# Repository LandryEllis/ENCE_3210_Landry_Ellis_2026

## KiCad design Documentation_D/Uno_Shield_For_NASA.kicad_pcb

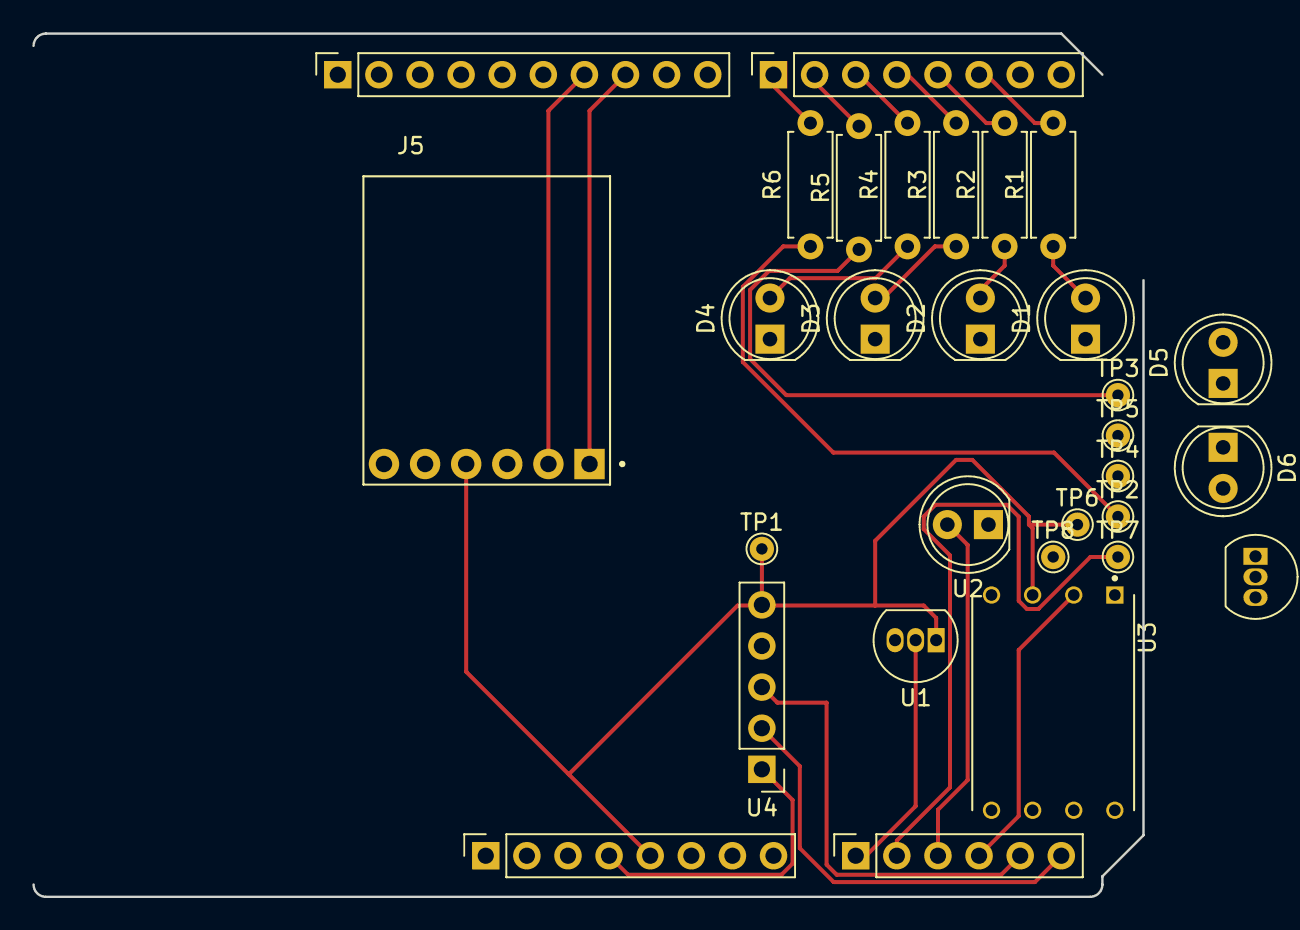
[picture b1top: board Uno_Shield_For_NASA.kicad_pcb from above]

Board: 2 copper layers, 68.6 x 53.3 mm, 30 parts (0 on the bottom side), 24 nets.

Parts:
D1: LED1_Onboard; LED_D5.0mm
D2: LED2_Onboard; LED_D5.0mm
D3: LED3_Onboard; LED_D5.0mm
D4: LED4_Onboard; LED_D5.0mm
D5: LED5_Remote; LED_D5.0mm
D6: LED6_Remote; LED_D5.0mm
J1: Power; PinSocket_1x08_P2.54mm_Vertical
J2: Digital/PWM; PinSocket_1x10_P2.54mm_Vertical
J3: Analog; PinSocket_1x06_P2.54mm_Vertical
J4: Digital/PWM; PinSocket_1x08_P2.54mm_Vertical
J5: OpenLog_MicroSD; MODULE_DEV-13955
R1, R2, R3, R4, R5, R6: 330; R_Axial_DIN0207_L6.3mm_D2.5mm_P7.62mm_Horizontal
TP1, TP2, TP3, TP4, TP6, TP7, TP8: ACC_Z_TestPoint; TestPoint_THTPad_D1.5mm_Drill0.7mm
TP5: GND; TestPoint_THTPad_D1.5mm_Drill0.7mm
U1: TMP36_Internal_A0; TO-92_Inline
U2: Humidity_A2; LED_D5.0mm
U3: Pressure_A3; DIP1330W46P254L1000H544Q8
U4: ADXL335_XY_A4_A5; PinHeader_1x05_P2.54mm_Vertical
U5: TMP36_External_A1; TO-92_Inline

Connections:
+3V3: J1.4, U4.1 (VCC)
+5V: J1.5, J5.4, TP6.1, U1.1 (Vs), U3.3 (OUT), U5.1 (Vs)
/A0: J3.1, U1.2 (Vout)
/A1: J3.2, TP7.1, U5.2 (Vout)
/A2: J3.3, U2.2 (OUT)
/A3: J3.4, U3.2 (Vs)
/A4: J3.5, U4.3 (X)
/A5: J3.6, U4.2 (GND)
/ACC_Z_SPARE: TP1.1, U4.5 (Z)
/D2: J4.6, R1.2
/D3: J4.5, R2.2
/D4: J4.4, R3.2
/D5: J4.3, R4.2
/D6: J4.2, R5.2
/D7: J4.1, R6.2
/D10: J2.8, J5.1
/D11: J2.7, J5.2
GND: D1.1 (K), D2.1 (K), D3.1 (K), D4.1 (K), D5.1 (K), D6.1 (K), J1.6, J1.7, J2.4, J5.3, TP4.1, TP5.1, TP8.1, U1.3 (GND), U2.1 (VCC), U3.1 (NC), U4.4 (Y), U5.3 (GND)
unnamed: D1.2 (A), R1.1
unnamed: D2.2 (A), R2.1
unnamed: D3.2 (A), R3.1
unnamed: D4.2 (A), R4.1
unnamed: D5.2 (A), R5.1, TP3.1
unnamed: D6.2 (A), R6.1, TP2.1

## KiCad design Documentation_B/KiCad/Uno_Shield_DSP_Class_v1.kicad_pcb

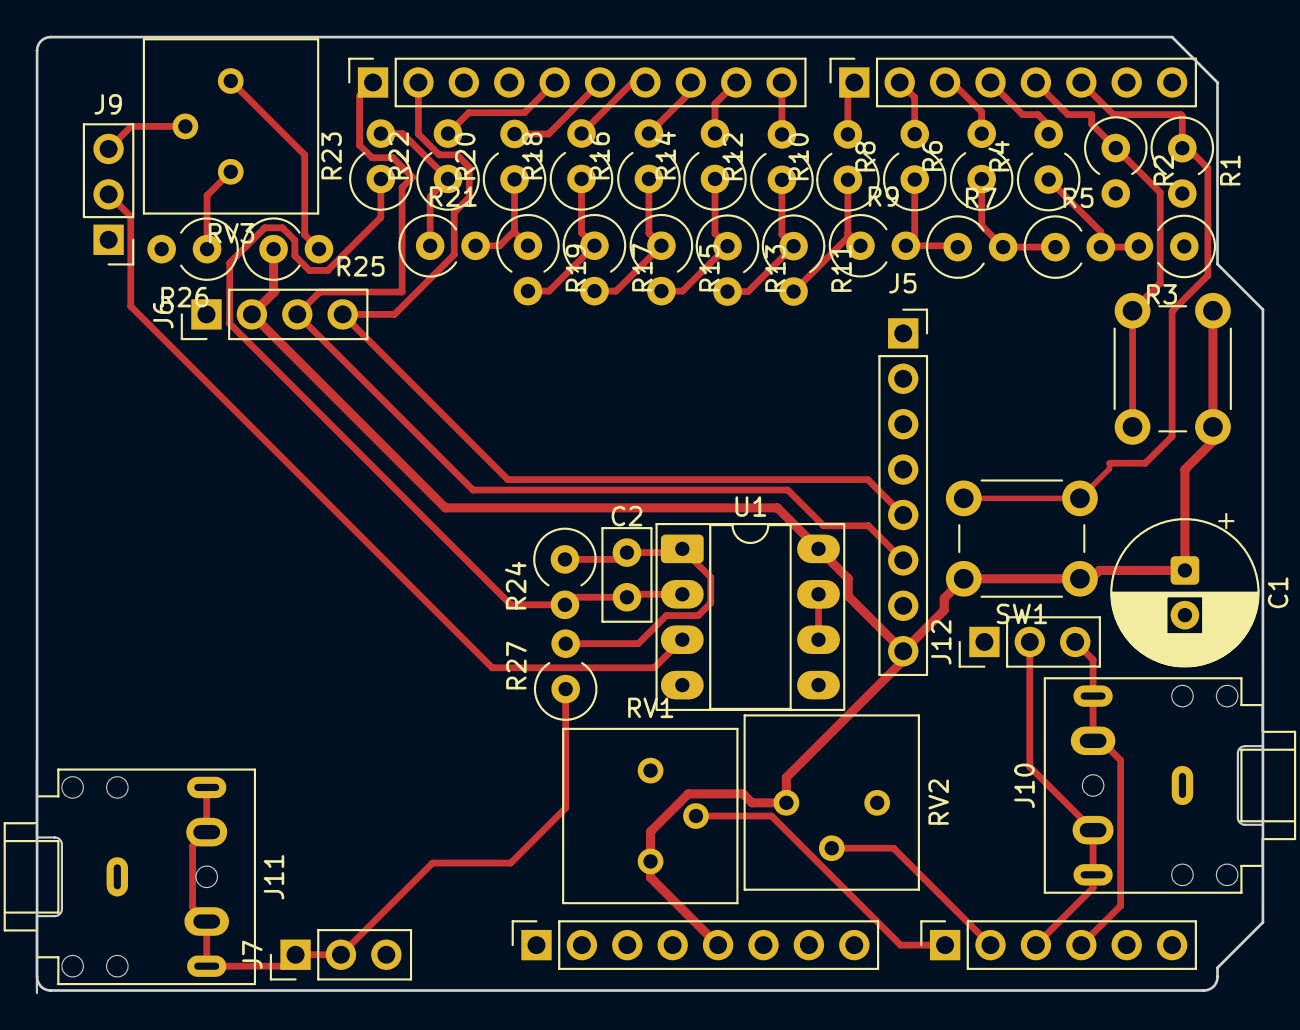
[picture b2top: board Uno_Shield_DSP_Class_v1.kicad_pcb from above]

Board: 2 copper layers, 68.6 x 53.3 mm, 46 parts (0 on the bottom side), 38 nets.

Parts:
C1: 47uF; CP_Radial_D8.0mm_P2.50mm
C2: 100pF; C_Disc_D5.0mm_W2.5mm_P2.50mm
J1: Power; PinSocket_1x08_P2.54mm_Vertical
J2: Digital/PWM; PinSocket_1x10_P2.54mm_Vertical
J3: Analog; PinSocket_1x06_P2.54mm_Vertical
J4: Digital/PWM; PinSocket_1x08_P2.54mm_Vertical
J5: IMU_CONN; PinSocket_1x08_P2.54mm_Vertical
J6: SCREEN_CONN; PinHeader_1x04_P2.54mm_Vertical
J7: AUDIO_OUT; PinHeader_1x03_P2.54mm_Vertical
J9: JUMPER; PinHeader_1x03_P2.54mm_Vertical
J10, J11: AudioJack5; Jack_3.5mm_CUI_SJ1-3525N_Horizontal
J12: AUDIO_IN; PinHeader_1x03_P2.54mm_Vertical
R1, R2: 100k; R_Axial_DIN0309_L9.0mm_D3.2mm_P2.54mm_Vertical
R3, R4, R6, R8, R10, R12, R14, R16, R18, R20, R22, R23, R24, R25, R26: 20k; R_Axial_DIN0309_L9.0mm_D3.2mm_P2.54mm_Vertical
R5, R7, R9, R11, R13, R15, R17, R19, R21: 10k; R_Axial_DIN0309_L9.0mm_D3.2mm_P2.54mm_Vertical
R27: 1k; R_Axial_DIN0309_L9.0mm_D3.2mm_P2.54mm_Vertical
RV1, RV2, RV3: 100k; Potentiometer_Bourns_3386P_Vertical
SW1: BT_1; SW_PUSH_6mm
SW2: BT_2; SW_PUSH_6mm
U1: MCP6002-xP; DIP-8_W7.62mm_Socket_LongPads

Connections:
+5V: C1.1, J1.5, J5.8, J6.2, R25.1, RV1.1, RV2.1, SW1.1, SW2.1, U1.8 (V+)
/A0: J3.1, RV1.2
/A1: J3.2, RV2.2
/AUDIO_OUT: J7.1, J7.2, J11.R, J11.RN, J11.T, J11.TN, R27.1
/BT1: J4.6, R1.1, SW1.2
/BT2: J4.5, R2.1, SW2.2
/D0: J4.4, R4.2
/D1: J4.3, R6.2
/D2: J4.2, R8.2
/D3: J4.1, R10.2
/D4: J2.10, R12.2
/D5: J2.9, R14.2
/D6: J2.8, R16.2
/D7: J2.7, R18.2
/D8: J2.6, R20.2
/D9: J2.5, R22.2
/IN_LEFT: J3.4, J10.T, J10.TN, J12.3
/IN_RIGHT: J3.3, J10.R, J10.RN, J12.2
/SCL: J2.1, J5.6, J6.3
/SDA: J2.2, J5.5, J6.4
GND: C1.2, J1.6, J1.7, J2.4, J5.7, J6.1, J7.3, J9.1, J10.S, J11.S, J12.1, R1.2, R2.2, R3.1, R26.2, RV1.3, RV2.3, U1.4 (V-), U1.5 (+)
unnamed: C2.2, R24.1, R27.2, U1.1
unnamed: J9.2, U1.3 (+)
unnamed: J9.3, RV3.2
unnamed: R3.2, R4.1, R5.2
unnamed: R5.1, R6.1, R7.2
unnamed: R7.1, R8.1, R9.2
unnamed: R9.1, R10.1, R11.2
unnamed: R11.1, R12.1, R13.2
unnamed: R13.1, R14.1, R15.2
unnamed: R15.1, R16.1, R17.2
unnamed: R17.1, R18.1, R19.2
unnamed: R19.1, R20.1, R21.2
unnamed: R21.1, R22.1, R23.2
unnamed: R25.2, RV3.1
unnamed: R26.1, RV3.3
unnamed: C2.1, R23.1, R24.2, U1.2 (-)
unnamed: U1.6 (-), U1.7

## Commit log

2026-01-09 mess
2026-01-12 Rename AveNotComplete.c to C-Workshop/AveNotComplete.c
2026-01-12 Rename Quadform3_not_complete.c to C-Workshop/Quadform3_not_complete.c
2026-01-12 Rename quadform.c to C-Workshop/quadform.c
2026-01-16 Rename test.txt to Lab_1/test.txt
2026-01-16 Update Readme with AI usage and testing notes
    Added notes on AI usage and testing challenges.
2026-02-03 Rename Documentation_B/DACpic.jpg to Documentation_B/DAC_Prototype/DACpic.jpg
2026-02-03 Rename Documentation_B/DAC.ino to Documentation_B/DAC_Prototype/DAC.ino
2026-02-03 Rename Documentation_B/Screenshot 2026-02-01 181107.png to Documentation_B/DAC_Prototype/SerialMonitor.png
2026-02-03 Rename Documentation_B/README.md to Documentation_B/KiCad/README.md
2026-02-03 Update STEP file for 10kΩ Trim Potentiometer
2026-02-03 Move STEP file for potentiometer to components folder
2026-02-03 Rename Documentation_B/KiCad/imu_dimensions.jpg to Documentation_B/KiCad/components/imu_dimensions.jpg
2026-02-03 Rename Documentation_B/KiCad/ITG-MPU.STEP to Documentation_B/KiCad/components/ITG-MPU.STEP
2026-02-03 Rename Documentation_B/KiCad/screen_dimensions.png to Documentation_B/KiCad/components/screen_dimensions.png
2026-02-03 Add OLED TEMU 0.96 in.stp to components directory
2026-02-03 Rename Documentation_B/KiCad/Readme to Documentation_B/KiCad/Arduino_MountingHole.pretty/Readme
2026-02-03 Add MountingHole_1.2mm.kicad_mod to Arduino directory
2026-02-03 Add MountingHole_3.2mm.kicad_mod to Arduino_MountingHole
2026-02-03 Rename Documentation_B/KiCad/components/imu_dimensions.jpg to Documentation_B/KiCad/components/MPU6050/imu_dimensions.jpg
2026-02-03 Rename Documentation_B/KiCad/components/screen_dimensions.png to Documentation_B/KiCad/components/OLED_096_in/screen_dimensions.png
2026-02-04 Add BOM for Uno Shield DSP Class v1
2026-02-04 Rename Documentation_B/KiCad/Screenshot 2026-02-04 154425.png to Documentation_B/KiCad/PCB_Layout/Screenshot 2026-02-04 154425.png
2026-02-04 Rename Documentation_B/KiCad/Screenshot 2026-02-04 155039.png to Documentation_B/KiCad/PCB_3D/Screenshot 2026-02-04 155039.png
2026-02-04 Rename Documentation_B/KiCad/Screenshot 2026-02-04 153331.png to Documentation_B/KiCad/Schematic/Screenshot 2026-02-04 153331.png
2026-02-04 Rename Documentation_B/KiCad/Screenshot 2026-02-04 155558.png to Documentation_B/KiCad/PCB_Back/Screenshot 2026-02-04 155558.png
2026-02-04 Rename Documentation_B/KiCad/Screenshot 2026-02-04 155604.png to Documentation_B/KiCad/PCB_Front/Screenshot 2026-02-04 155604.png
2026-02-04 Rename FrontScreenshot 2026-02-04 155604.png to Screenshot 2026-02-04 155604.png
2026-03-13 Rename Documentation_D/README.md to Documentation_D/Schematic/README.md
2026-03-13 Add README for PCB Layout documentation
2026-03-13 Rename Arduino Shield for NASA Balloon.pdf to Presentation: Arduino Shield for NASA Balloon.pdf
2026-03-13 Rename Arduino Shield for NASA Balloon (1).pdf to Presentation: Arduino Shield for NASA Balloon (1).pdf
